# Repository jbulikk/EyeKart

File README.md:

# EyeKart

A gimbal system that mimics the user's head movements in real time.
The project is divided into two cooperating parts: a transmitting unit and a receiving unit.

- The transmitting module uses an IMU sensor to capture the user's head orientation.

- The motion data is processed and wirelessly transmitted to the receiving module.

- The receiving module interprets the incoming data and controls servo motors to adjust the mechanical gimbal accordingly, replicating the user's head movement.

# Overview

🎥 [Demo 1](https://youtu.be/xsn1YAiG0OE)  
🎥 [Demo 2](https://youtu.be/Qv6_rfJNsOU)

<br/>

<br/>

<br/>

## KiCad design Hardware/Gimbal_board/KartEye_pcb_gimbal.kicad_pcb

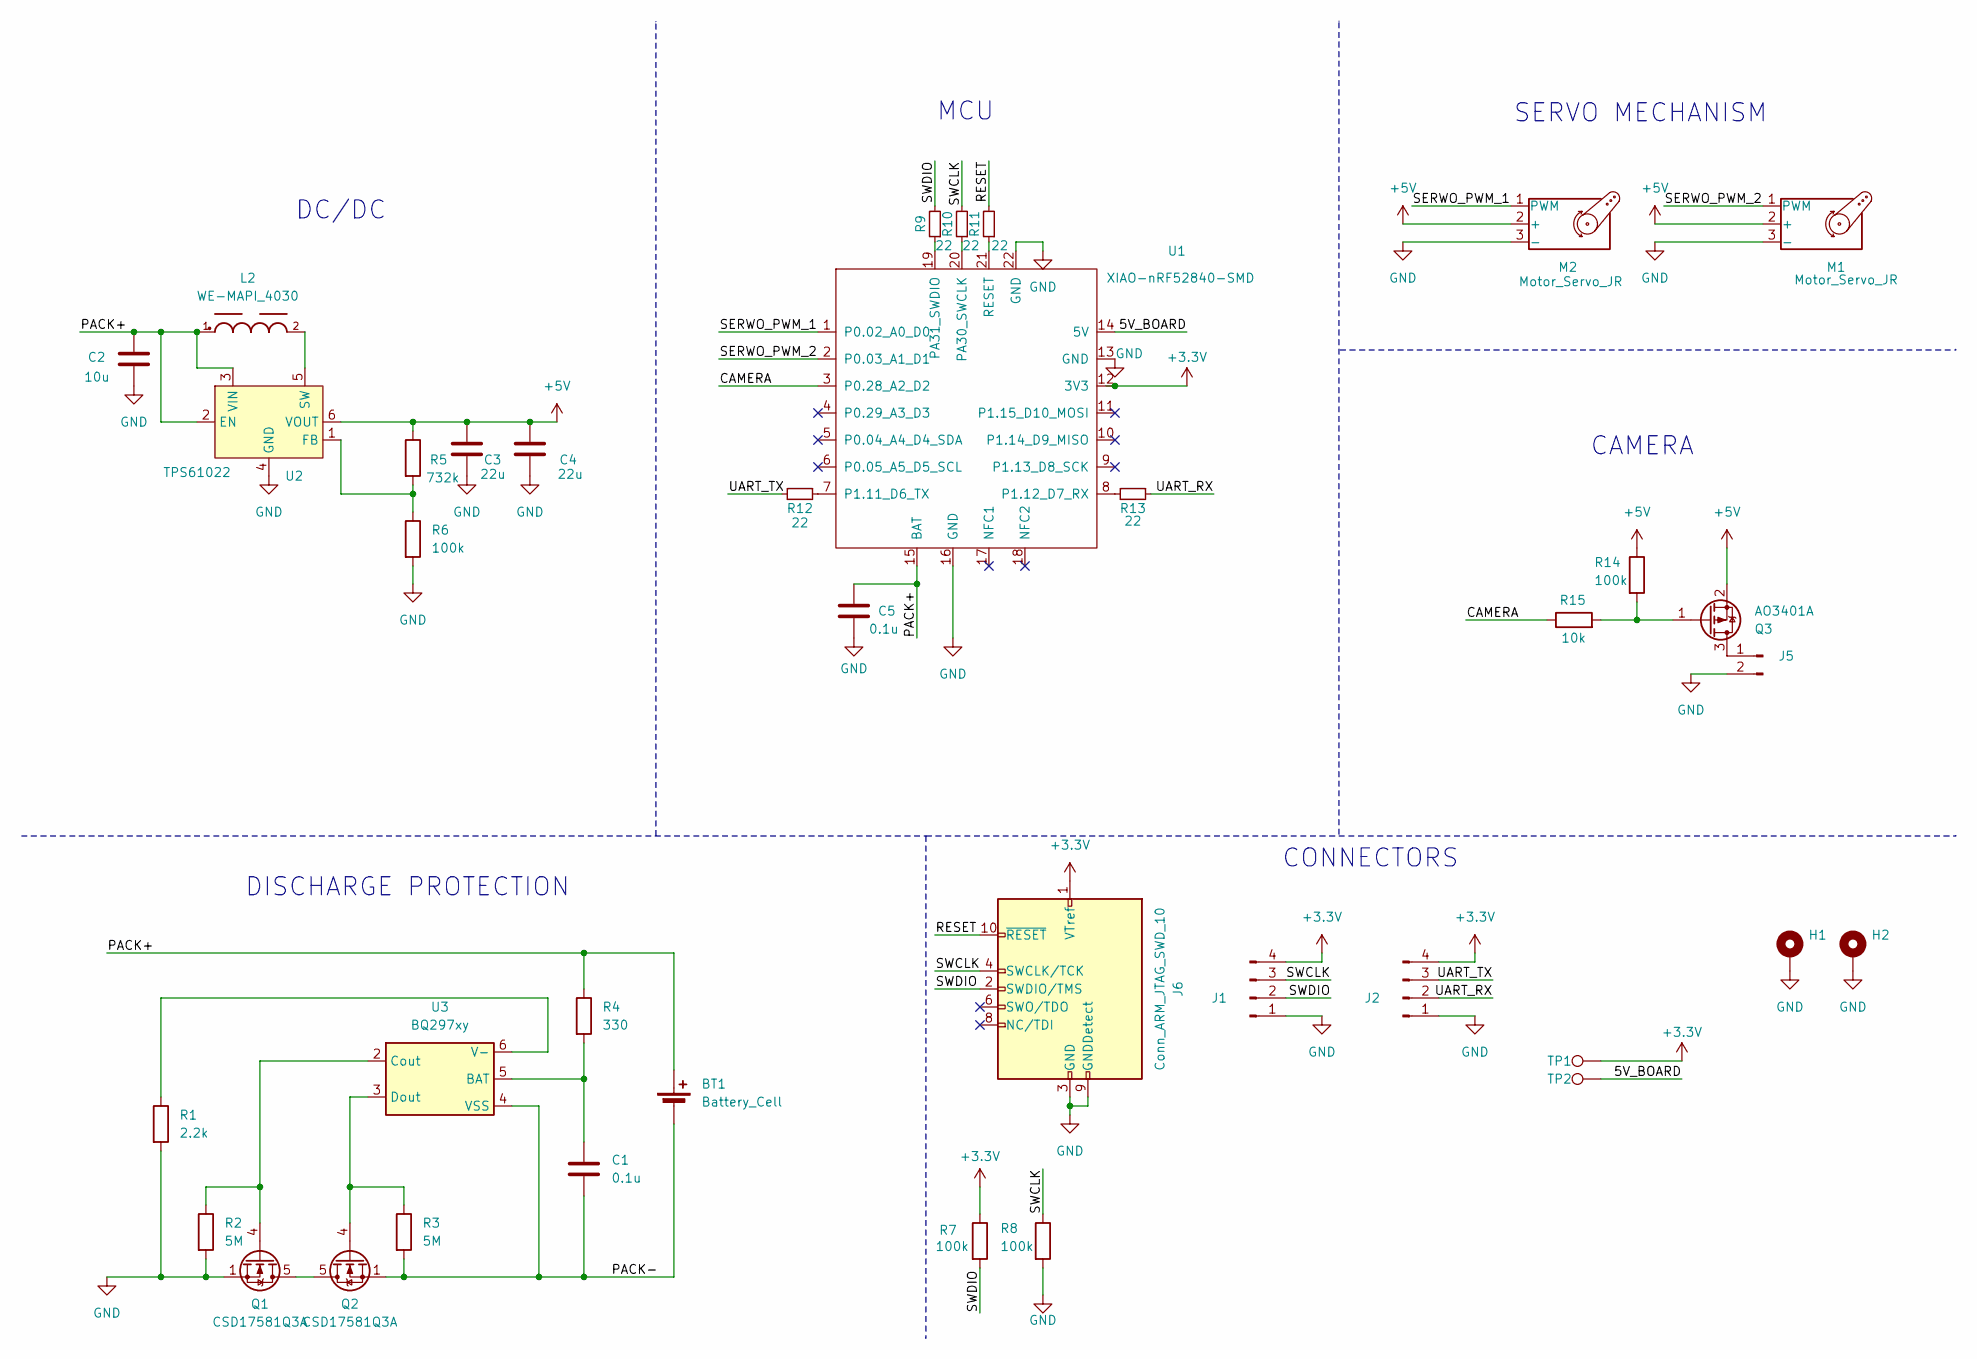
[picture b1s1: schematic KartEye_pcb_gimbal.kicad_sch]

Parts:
BT1: Battery_Cell; JST_XH_B2B-XH-A_1x02_P2.50mm_Vertical
C1, C5: 0.1u; C_0805_2012Metric_Pad1.18x1.45mm_HandSolder
C2: 10u; C_0805_2012Metric_Pad1.18x1.45mm_HandSolder
C3, C4: 22u; C_0805_2012Metric_Pad1.18x1.45mm_HandSolder
H1, H2: MountingHole_Pad; MountingHole_2.2mm_M2_DIN965_Pad
J1, J2: Conn_01x04_Pin; PinHeader_1x04_P2.54mm_Vertical
J5: Conn_01x02_Pin; Molex_PicoBlade_53047-0210_1x02_P1.25mm_Vertical
J6: Conn_ARM_JTAG_SWD_10; PinHeader_2x05_P1.27mm_Vertical_SMD
L2: WE-MAPI_4030
M1, M2: Motor_Servo_JR; PinHeader_1x03_P2.54mm_Vertical
Q1, Q2: CSD17581Q3A; VSON-8_3.3x3.3mm_P0.65mm_NexFET
Q3: AO3401A; SOT-23
R1: 2.2k; R_0805_2012Metric_Pad1.20x1.40mm_HandSolder
R2, R3: 5M; R_0805_2012Metric_Pad1.20x1.40mm_HandSolder
R4: 330; R_0805_2012Metric_Pad1.20x1.40mm_HandSolder
R5: 732k; R_0805_2012Metric_Pad1.20x1.40mm_HandSolder
R6, R7, R8, R14: 100k; R_0805_2012Metric_Pad1.20x1.40mm_HandSolder
R9, R10, R11, R12, R13: 22; R_0805_2012Metric_Pad1.20x1.40mm_HandSolder
R15: 10k; R_0805_2012Metric_Pad1.20x1.40mm_HandSolder
TP1, TP2: TestPoint; TestPoint_Pad_1.0x1.0mm
U1: XIAO-nRF52840-SMD
U2: TPS61022; SOT-563
U3: BQ297xy; WSON-6_1.5x1.5mm_P0.5mm

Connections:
+3.3V: J1.4, J2.4, J6.1 (VTref), R7.1, TP1.1, U1.12 (3V3)
+5V: C3.1, C4.1, M1.2 (+), M2.2 (+), Q3.2 (S), R5.1, R14.1, U2.6 (VOUT)
/5V_BOARD: TP2.1, U1.14 (5V)
/CAMERA: R15.1, U1.3 (P0.28_A2_D2)
/PACK+: BT1.1 (+), C2.1, C5.1, L2.1, R4.1, U1.15 (BAT), U2.2 (EN), U2.3 (VIN)
/PACK-: BT1.2 (-), C1.2, Q2.1 (S), Q2.2 (S), Q2.3 (S), R3.2, U3.4 (VSS)
/RESET: J6.10 (~RESET), R11.2
/SERWO_PWM_1: M2.1 (PWM), U1.1 (P0.02_A0_D0)
/SERWO_PWM_2: M1.1 (PWM), U1.2 (P0.03_A1_D1)
/SWCLK: J1.3, J6.4 (SWCLK/TCK), R8.1, R10.2
/SWDIO: J1.2, J6.2 (SWDIO/TMS), R7.2, R9.2
/UART_RX: J2.2, R13.1
/UART_TX: J2.3, R12.2
GND: C2.2, C3.2, C4.2, C5.2, H1.1, H2.1, J1.1, J2.1, J5.2, J6.3 (GND), J6.5 (GND), J6.9 (GNDDetect), M1.3 (-), M2.3 (-), Q1.1 (S), Q1.2 (S), Q1.3 (S), R1.2, R2.2, R6.2, R8.2, U1.13 (GND), U1.16 (GND), U1.22 (GND), U2.4 (GND)
unnamed: J5.1, Q3.3 (D)
unnamed: Q1.5 (D), Q2.5 (D)
unnamed: Q1.4 (G), R2.1, U3.2 (Cout)
unnamed: Q2.4 (G), R3.1, U3.3 (Dout)
unnamed: Q3.1 (G), R14.2, R15.2
unnamed: R12.1, U1.7 (P1.11_D6_TX)
unnamed: R13.2, U1.8 (P1.12_D7_RX)
unnamed: R10.1, U1.20 (PA30_SWCLK)
unnamed: R9.1, U1.19 (PA31_SWDIO)
unnamed: R11.1, U1.21 (RESET)
unnamed: R5.2, R6.1, U2.1 (FB)
unnamed: L2.2, U2.5 (SW)
unnamed: C1.1, R4.2, U3.5 (BAT)
unnamed: R1.1, U3.6 (V-)

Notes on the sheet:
CONNECTORS
SERVO MECHANISM
DC/DC
MCU
DISCHARGE PROTECTION
CAMERA

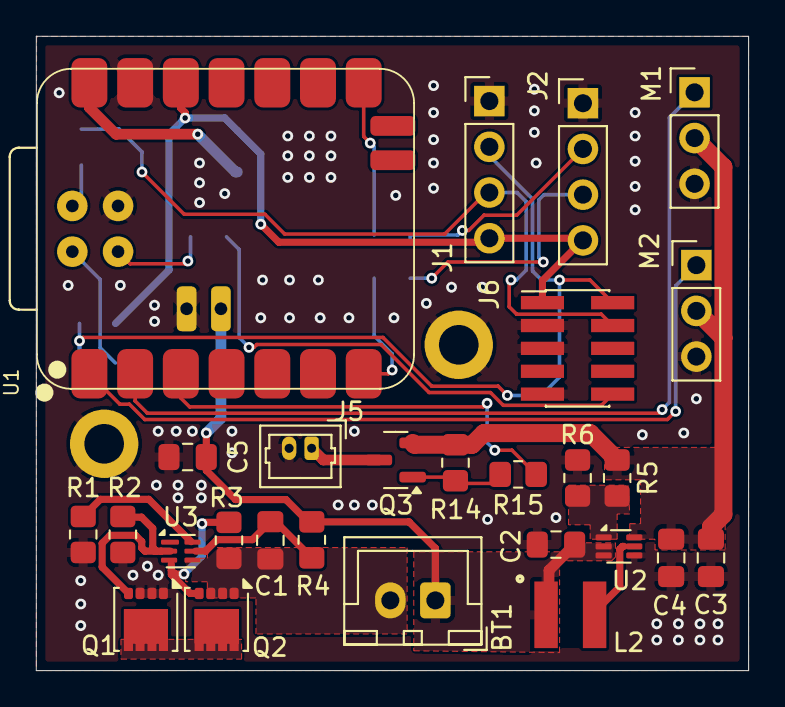
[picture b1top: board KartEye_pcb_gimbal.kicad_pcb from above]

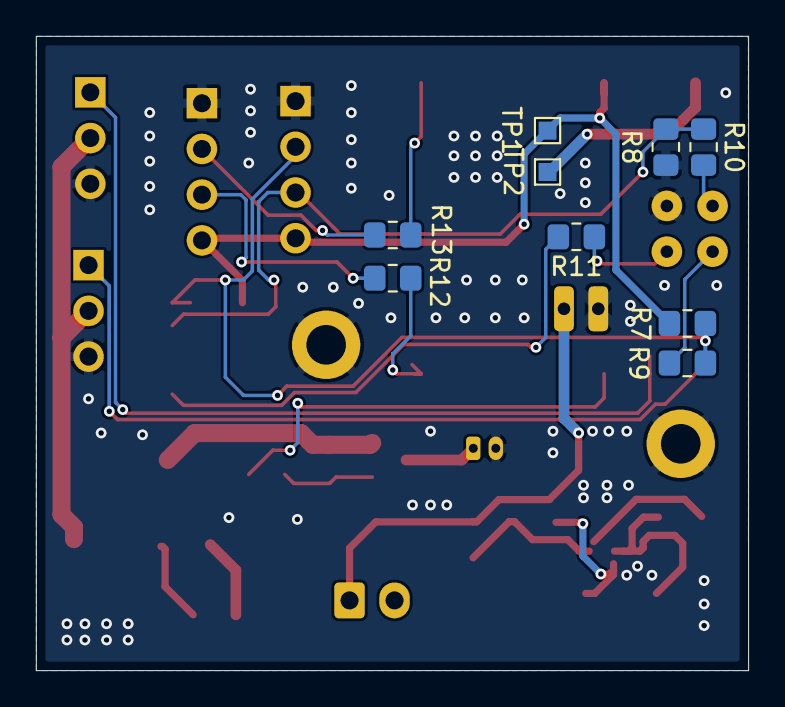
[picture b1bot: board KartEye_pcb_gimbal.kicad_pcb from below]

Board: 2 copper layers, 39.6 x 35.2 mm, 38 parts (9 on the bottom side), 28 nets.

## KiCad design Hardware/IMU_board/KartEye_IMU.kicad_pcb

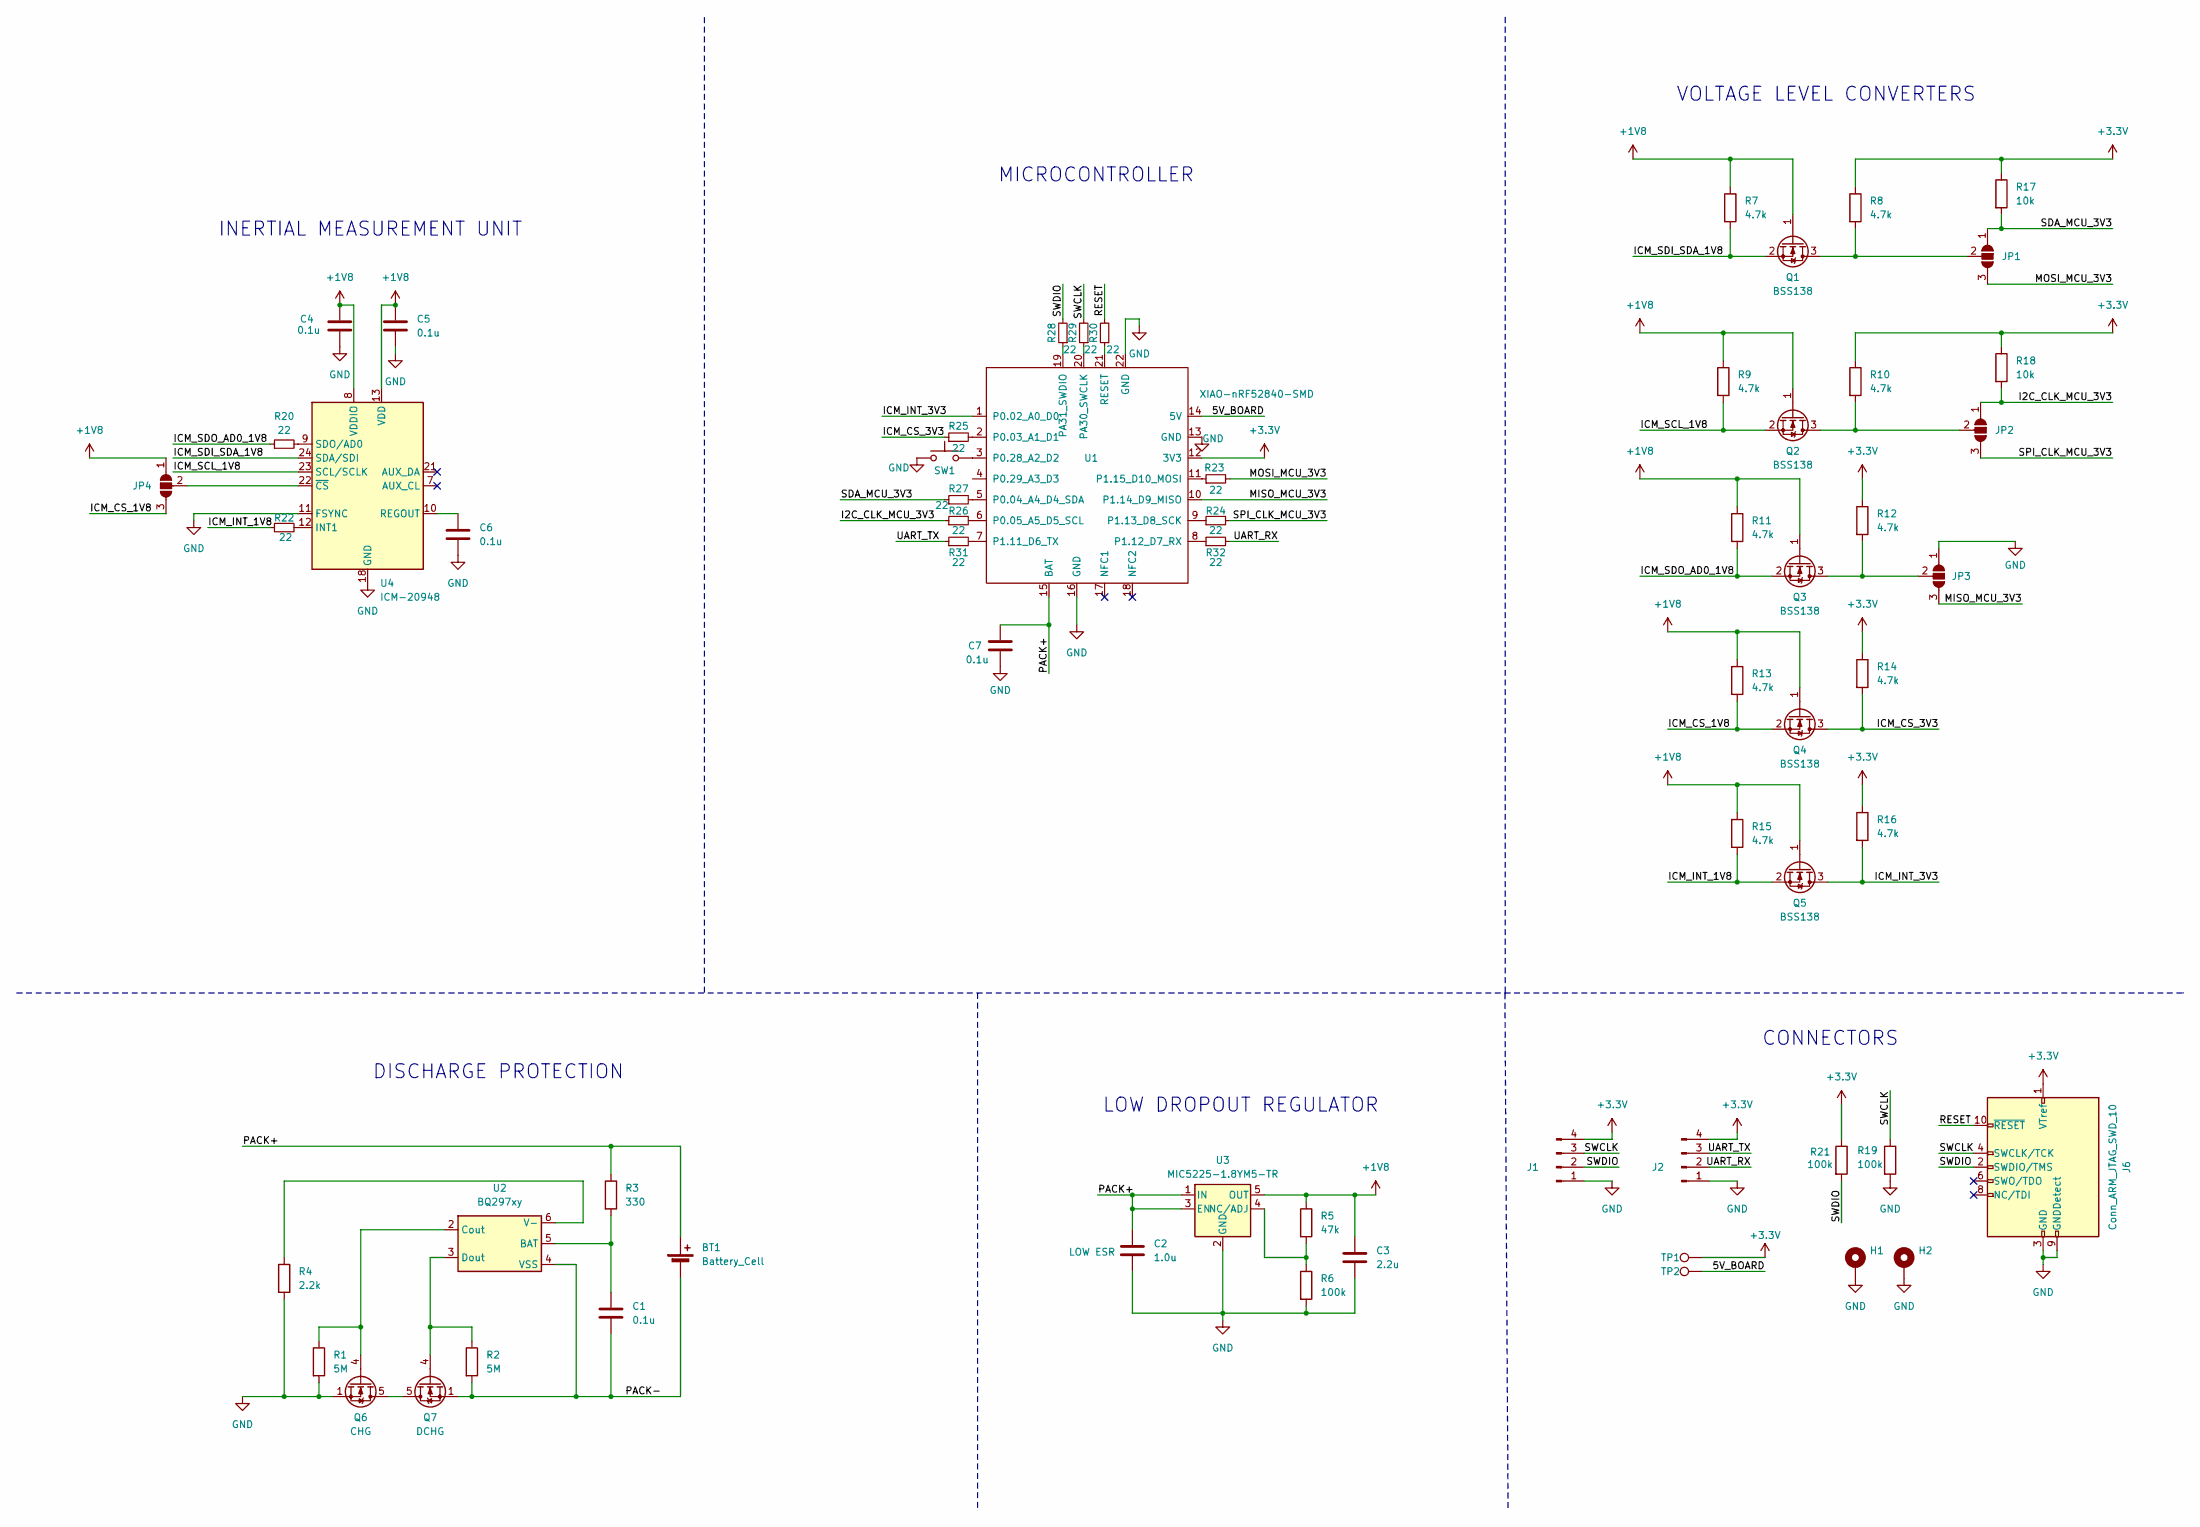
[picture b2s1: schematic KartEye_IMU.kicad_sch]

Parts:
BT1: Battery_Cell; JST_XH_B2B-XH-A_1x02_P2.50mm_Vertical
C1, C4, C5, C6, C7: 0.1u; C_0805_2012Metric_Pad1.18x1.45mm_HandSolder
C2: 1.0u; C_0805_2012Metric_Pad1.18x1.45mm_HandSolder
C3: 2.2u; C_0805_2012Metric_Pad1.18x1.45mm_HandSolder
H1, H2: MountingHole_Pad; MountingHole_2.2mm_M2_DIN965_Pad
J1, J2: Conn_01x04_Pin; PinHeader_1x04_P2.54mm_Vertical
J6: Conn_ARM_JTAG_SWD_10; PinHeader_2x05_P1.27mm_Vertical_SMD
JP1, JP2, JP3, JP4: SolderJumper_3_Open; SolderJumper-3_P1.3mm_Open_RoundedPad1.0x1.5mm_NumberLabels
Q1, Q2, Q3, Q4, Q5: BSS138; SOT-23_Handsoldering
Q6: CHG; VSON-8_3.3x3.3mm_P0.65mm_NexFET
Q7: DCHG; VSON-8_3.3x3.3mm_P0.65mm_NexFET
R1, R2: 5M; R_0805_2012Metric_Pad1.20x1.40mm_HandSolder
R3: 330; R_0805_2012Metric_Pad1.20x1.40mm_HandSolder
R4: 2.2k; R_0805_2012Metric_Pad1.20x1.40mm_HandSolder
R5: 47k; R_0805_2012Metric_Pad1.20x1.40mm_HandSolder
R6, R19, R21: 100k; R_0805_2012Metric_Pad1.20x1.40mm_HandSolder
R7, R8, R9, R10, R11, R12, R13, R14, R15, R16: 4.7k; R_0805_2012Metric_Pad1.20x1.40mm_HandSolder
R17, R18: 10k; R_0805_2012Metric_Pad1.20x1.40mm_HandSolder
R20, R22, R23, R24, R25, R26, R27, R28, R29, R30, R31, R32: 22; R_0805_2012Metric_Pad1.20x1.40mm_HandSolder
SW1: SW_Push; SW_SPST_CK_RS282G05A3
TP1, TP2: TestPoint; TestPoint_Pad_1.0x1.0mm
U1: XIAO-nRF52840-SMD
U2: BQ297xy; WSON-6_1.5x1.5mm_P0.5mm
U3: MIC5225-1.8YM5-TR; SOT-23-5
U4: ICM-20948; InvenSense_QFN-24_3x3mm_P0.4mm

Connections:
+1V8: C3.1, C4.1, C5.1, JP4.1 (A), Q1.1 (G), Q2.1 (G), Q3.1 (G), Q4.1 (G), Q5.1 (G), R5.1, R7.1, R9.1, R11.1, R13.1, R15.1, U3.5 (OUT), U4.8 (VDDIO), U4.13 (VDD)
+3.3V: J1.4, J2.4, J6.1 (VTref), R8.1, R10.1, R12.1, R14.1, R16.1, R17.1, R18.1, R21.1, TP1.1, U1.12 (3V3)
/5V_BOARD: TP2.1, U1.14 (5V)
/I2C_CLK_MCU_3V3: JP2.1 (A), R18.2, R26.1
/ICM_CS_1V8: JP4.3 (B), Q4.2 (S), R13.2
/ICM_CS_3V3: Q4.3 (D), R14.2, R25.1
/ICM_INT_1V8: Q5.2 (S), R15.2, R22.1
/ICM_INT_3V3: Q5.3 (D), R16.2, U1.1 (P0.02_A0_D0)
/ICM_SCL_1V8: Q2.2 (S), R9.2, U4.23 (SCL/SCLK)
/ICM_SDI_SDA_1V8: Q1.2 (S), R7.2, U4.24 (SDA/SDI)
/ICM_SDO_AD0_1V8: Q3.2 (S), R11.2, R20.1
/MISO_MCU_3V3: JP3.3 (B), U1.10 (P1.14_D9_MISO)
/MOSI_MCU_3V3: JP1.3 (B), R23.2
/PACK+: BT1.1 (+), C2.1, C7.1, R3.1, U1.15 (BAT), U3.1 (IN), U3.3 (EN)
/PACK-: BT1.2 (-), C1.2, Q7.1 (S), Q7.2 (S), Q7.3 (S), R2.2, U2.4 (VSS)
/RESET: J6.10 (~RESET), R30.2
/SDA_MCU_3V3: JP1.1 (A), R17.2, R27.1
/SPI_CLK_MCU_3V3: JP2.3 (B), R24.2
/SWCLK: J1.3, J6.4 (SWCLK/TCK), R19.1, R29.2
/SWDIO: J1.2, J6.2 (SWDIO/TMS), R21.2, R28.2
/UART_RX: J2.2, R32.2
/UART_TX: J2.3, R31.1
GND: C2.2, C3.2, C4.2, C5.2, C6.2, C7.2, H1.1, H2.1, J1.1, J2.1, J6.3 (GND), J6.5 (GND), J6.9 (GNDDetect), JP3.1 (A), Q6.1 (S), Q6.2 (S), Q6.3 (S), R1.2, R4.2, R6.2, R19.2, SW1.1, U1.13 (GND), U1.16 (GND), U1.22 (GND), U3.2 (GND), U4.11 (FSYNC), U4.18 (GND), U4.20 (GND)
unnamed: JP1.2 (C), Q1.3 (D), R8.2
unnamed: JP2.2 (C), Q2.3 (D), R10.2
unnamed: JP3.2 (C), Q3.3 (D), R12.2
unnamed: JP4.2 (C), U4.22 (~CS)
unnamed: Q6.5 (D), Q7.5 (D)
unnamed: Q6.4 (G), R1.1, U2.2 (Cout)
unnamed: Q7.4 (G), R2.1, U2.3 (Dout)
unnamed: R25.2, U1.2 (P0.03_A1_D1)
unnamed: R27.2, U1.5 (P0.04_A4_D4_SDA)
unnamed: R26.2, U1.6 (P0.05_A5_D5_SCL)
unnamed: SW1.2, U1.3 (P0.28_A2_D2)
unnamed: R31.2, U1.7 (P1.11_D6_TX)
unnamed: R32.1, U1.8 (P1.12_D7_RX)
unnamed: R24.1, U1.9 (P1.13_D8_SCK)
unnamed: R23.1, U1.11 (P1.15_D10_MOSI)
unnamed: R29.1, U1.20 (PA30_SWCLK)
unnamed: R28.1, U1.19 (PA31_SWDIO)
unnamed: R30.1, U1.21 (RESET)
unnamed: C1.1, R3.2, U2.5 (BAT)
unnamed: R4.1, U2.6 (V-)
unnamed: R5.2, R6.1, U3.4 (NC/ADJ)
unnamed: R22.2, U4.12 (INT1)
unnamed: C6.1, U4.10 (REGOUT)
unnamed: R20.2, U4.9 (SDO/AD0)

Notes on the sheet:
INERTIAL MEASUREMENT UNIT
LOW DROPOUT REGULATOR
DISCHARGE PROTECTION
VOLTAGE LEVEL CONVERTERS
CONNECTORS
MICROCONTROLLER

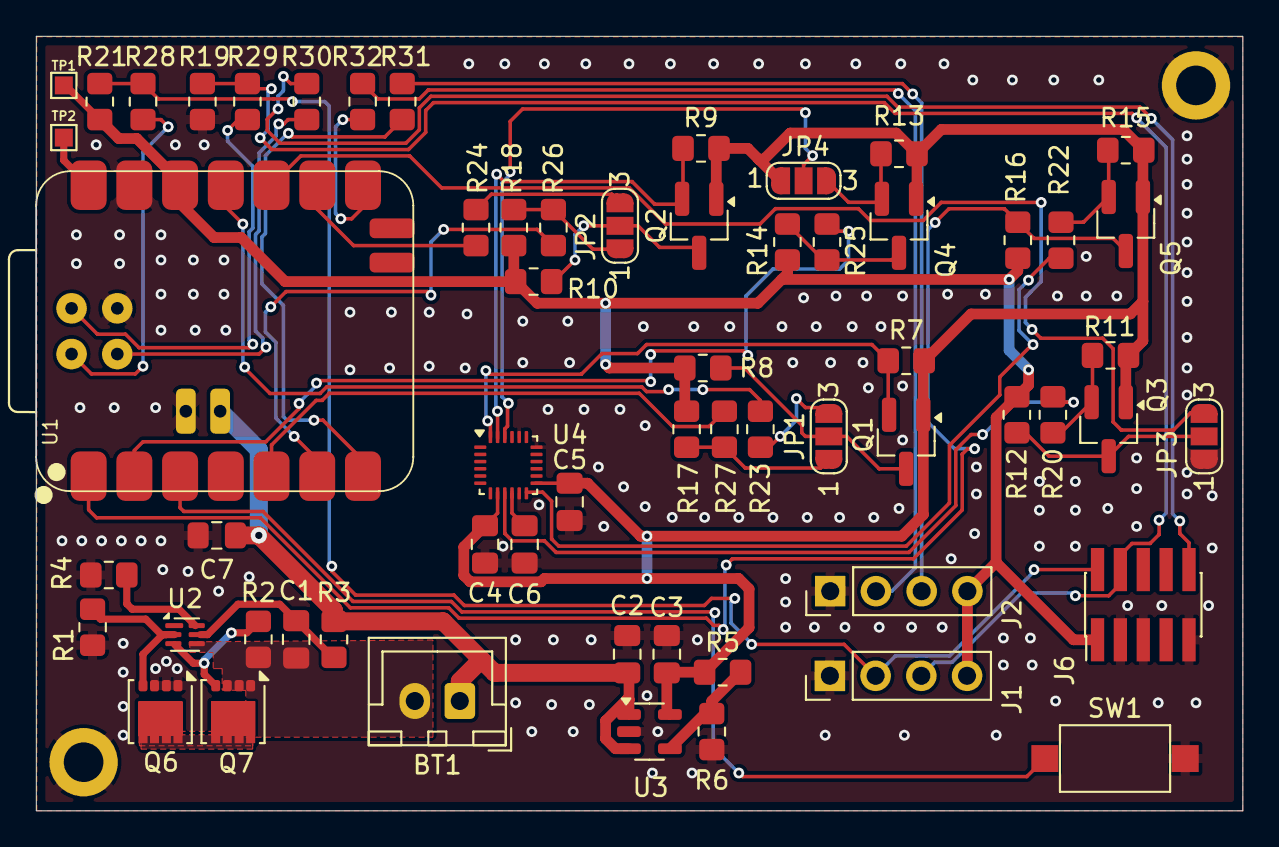
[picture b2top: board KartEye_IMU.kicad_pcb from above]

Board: 2 copper layers, 67.0 x 43.0 mm, 63 parts (0 on the bottom side), 47 nets.

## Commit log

2025-03-29 Create README.md
    initial commit
2025-06-03 initial code
2025-06-06 reading who_am_i and scanning i2c
2025-06-06 restore main
2025-06-06 i2c_scanner
2025-06-06 test commit
2025-06-07 working ICM
2025-06-07 add servo files
2025-06-07 working calculating pitch and yaw, enabled printing float values
2025-06-07 Imu with BT protocol
2025-06-08 adjusting complementary filter
2025-06-08 update gitignore, fix errors
2025-06-08 imu board main
2025-06-08 fix errors
2025-06-08 fix gimbal initilization
2025-06-08 send both angles, disable time print
2025-06-08 set gimbal
2025-06-08 add ciritical section
2025-06-08 send as intx100, change alpha
2025-06-08 add yaw
2025-06-08 use int parsing
2025-06-08 send bt each 50ms
2025-06-08 parse 3 values
2025-06-08 working
2025-06-08 calibrate gyro, change alpha
2025-06-08 add cal button
2025-06-08 add camera
2025-06-08 cleaning code
2025-07-13 Adding hardware files
